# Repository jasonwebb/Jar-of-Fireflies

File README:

# Jar of Fireflies

Reinvention of the classic "Jar of fireflies" project using the Arduino framework and the ATTiny85 microcontroller. Includes six charlieplexed LEDs, a piezo sensor and a variety of powering options.

Mason jars outfitted with LEDs and a small microcontroller programmed to mimic the behavior of fireflies caught on a warm summer night. The addition of a piezo sensor enables a degree of interactivity that everyone wished their jars did as kids; tap the jar, and the lights react! Based on an old project found on Instructables, this project includes a number of great updates, including Arduino compatibility, interactivity and easier-to-use parts! Plus, the entire project embraces the principles of Open Source Hardware (OSHW), which means you can learn from and modify all of the code, design files, schematics and more for free!

## Board features
* ATTiny85 microcontroller mounted with a DIP IC socket, so it can be easily removed and reprogrammed externally using HLT's Arduino bootloader (see http://hlt.media.mit.edu/?p=1695).
* Six charlieplexed LEDs (with the option to use SMD LEDs with fancy soldering).
* Piezo sensor to detect tapping for interaction.
* 2-pin header for power, so external breakout boards for various power options can be added (DC barrel jack, USB mini-B, 2xAA batteries and solar cell).
* Contacts for alligator clips so multiple jars can be daisychained to a single power source.

## More information
* Author website: http://jason-webb.info
* Wiki: http://jason-webb.info/wiki/index.php?title=Jar_of_Fireflies

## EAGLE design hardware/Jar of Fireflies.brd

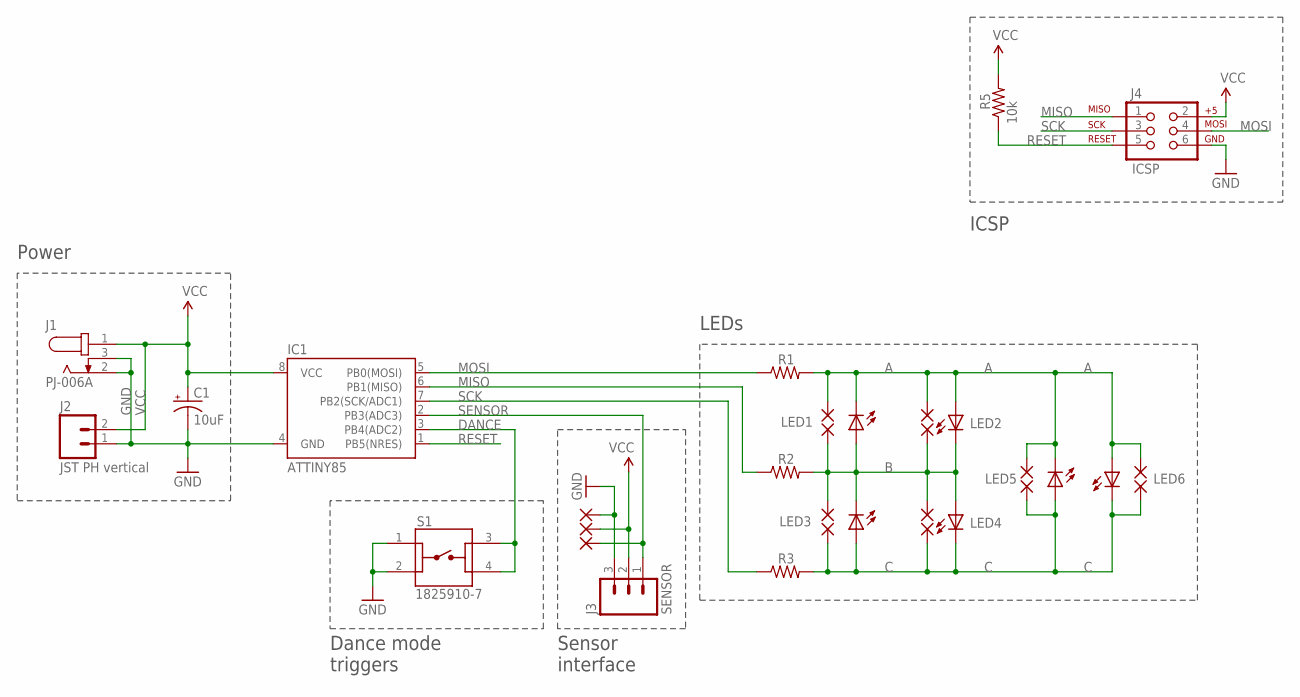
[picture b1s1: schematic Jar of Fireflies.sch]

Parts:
C1: 10uF; CPOL-RADIAL-10UF-25V
IC1: ATTINY85; DIP08
J1: PJ-006A; CUI_PJ-006A
J2: JST PH vertical; JST-2-PTH-VERT
J3: SENSOR; 1X03
J4: ICSP; 2X3_LOCK
LED1, LED2, LED3, LED4, LED5, LED6: Amber; LED5MM
PAD1, PAD2, PAD3, PAD4, PAD5, PAD6, PAD7, PAD8, PAD9, PAD10, PAD11, PAD12: SMD2; SMD1,27-2,54
PAD13, PAD14, PAD15: WIREPADSMD1,27-254; SMD1,27-2,54
R1, R2, R3: 150; 0207/2V
R5: 10k; 0207/2V
S1: 1825910-7; SW_1825910-7

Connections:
A: LED1.K (C), LED2.A, LED5.K (C), LED6.A, PAD1.1, PAD5.1, PAD9.1, PAD11.1, R1.2
B: LED1.A, LED2.K (C), LED3.K (C), LED4.A, PAD2.1, PAD3.1, PAD6.1, PAD7.1, R2.2
C: LED3.A, LED4.K (C), LED5.A, LED6.K (C), PAD4.1, PAD8.1, PAD10.1, PAD12.1, R3.2
DANCE: IC1.3 (PB4(ADC2)), S1.3, S1.4
GND: C1.2 (-), IC1.4 (GND), J1.2, J1.3, J2.1, J3.3, J4.6, PAD13.1, S1.1, S1.2
MISO: IC1.6 (PB1(MISO)), J4.1, R2.1
MOSI: IC1.5 (PB0(MOSI)), J4.4, R1.1
RESET: IC1.1 (PB5(NRES)), J4.5, R5.1
SCK: IC1.7 (PB2(SCK/ADC1)), J4.3, R3.1
SENSOR: IC1.2 (PB3(ADC3)), J3.1, PAD15.1
VCC: C1.1 (+), IC1.8 (VCC), J1.1, J2.2, J3.2, J4.2, PAD14.1, R5.2

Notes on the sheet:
ICSP
Power
Dance mode triggers
Sensor interface
LEDs

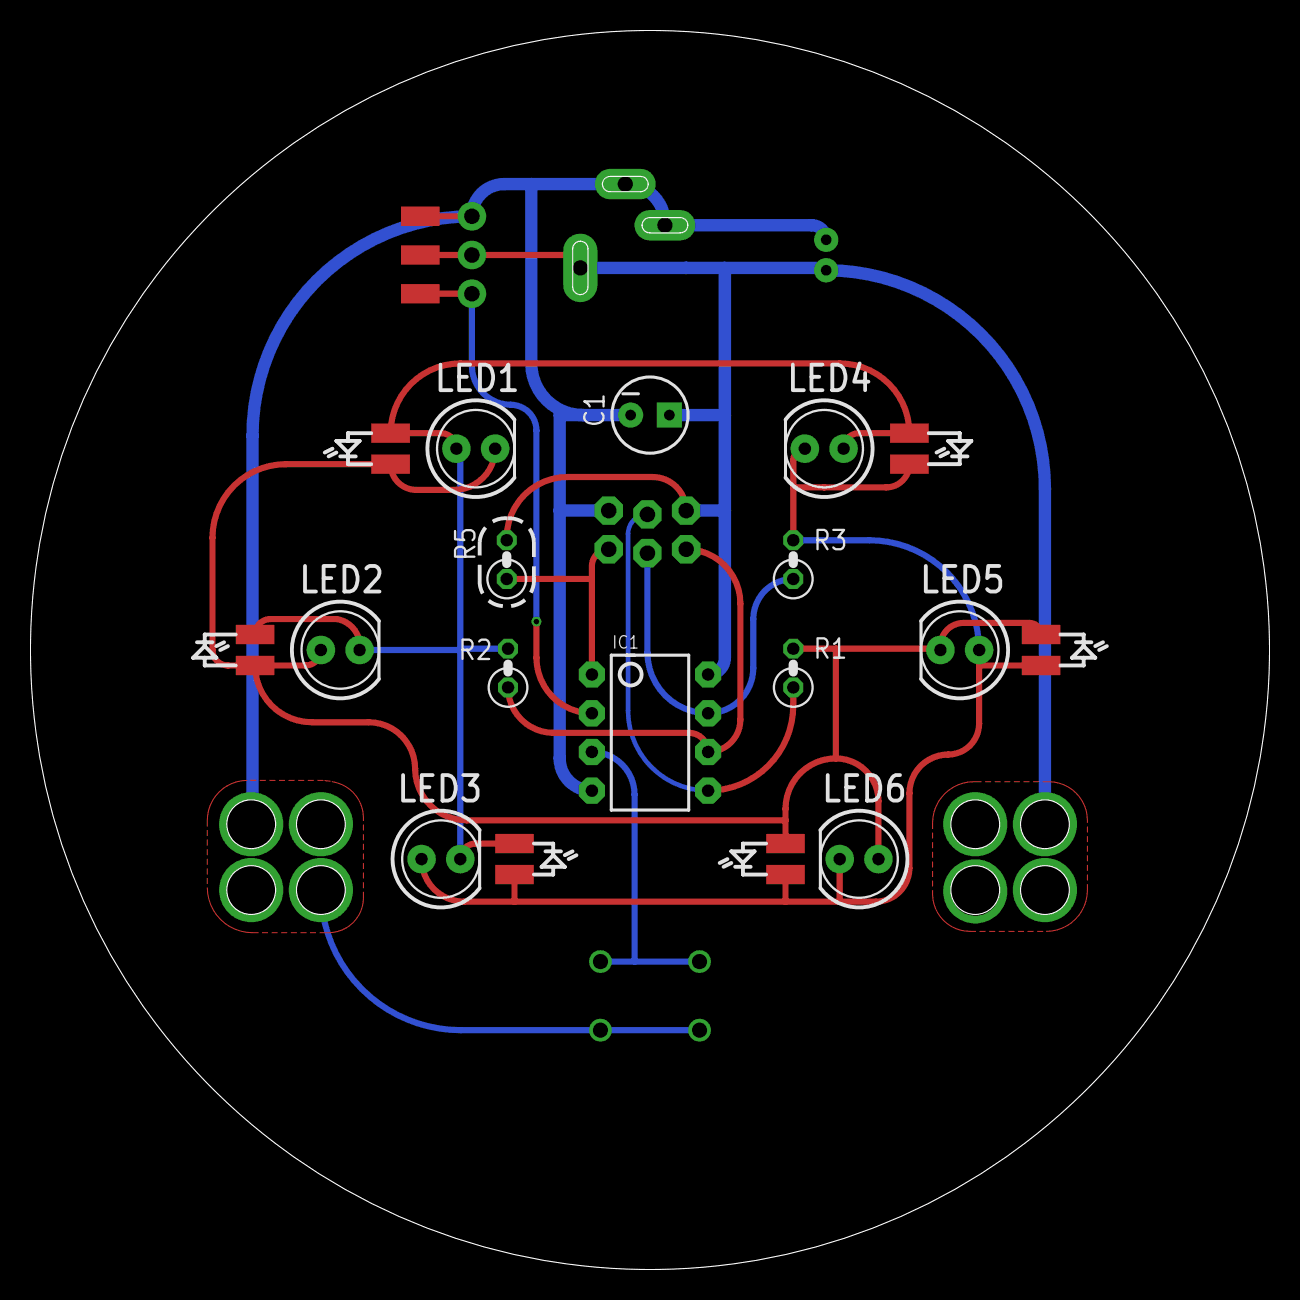
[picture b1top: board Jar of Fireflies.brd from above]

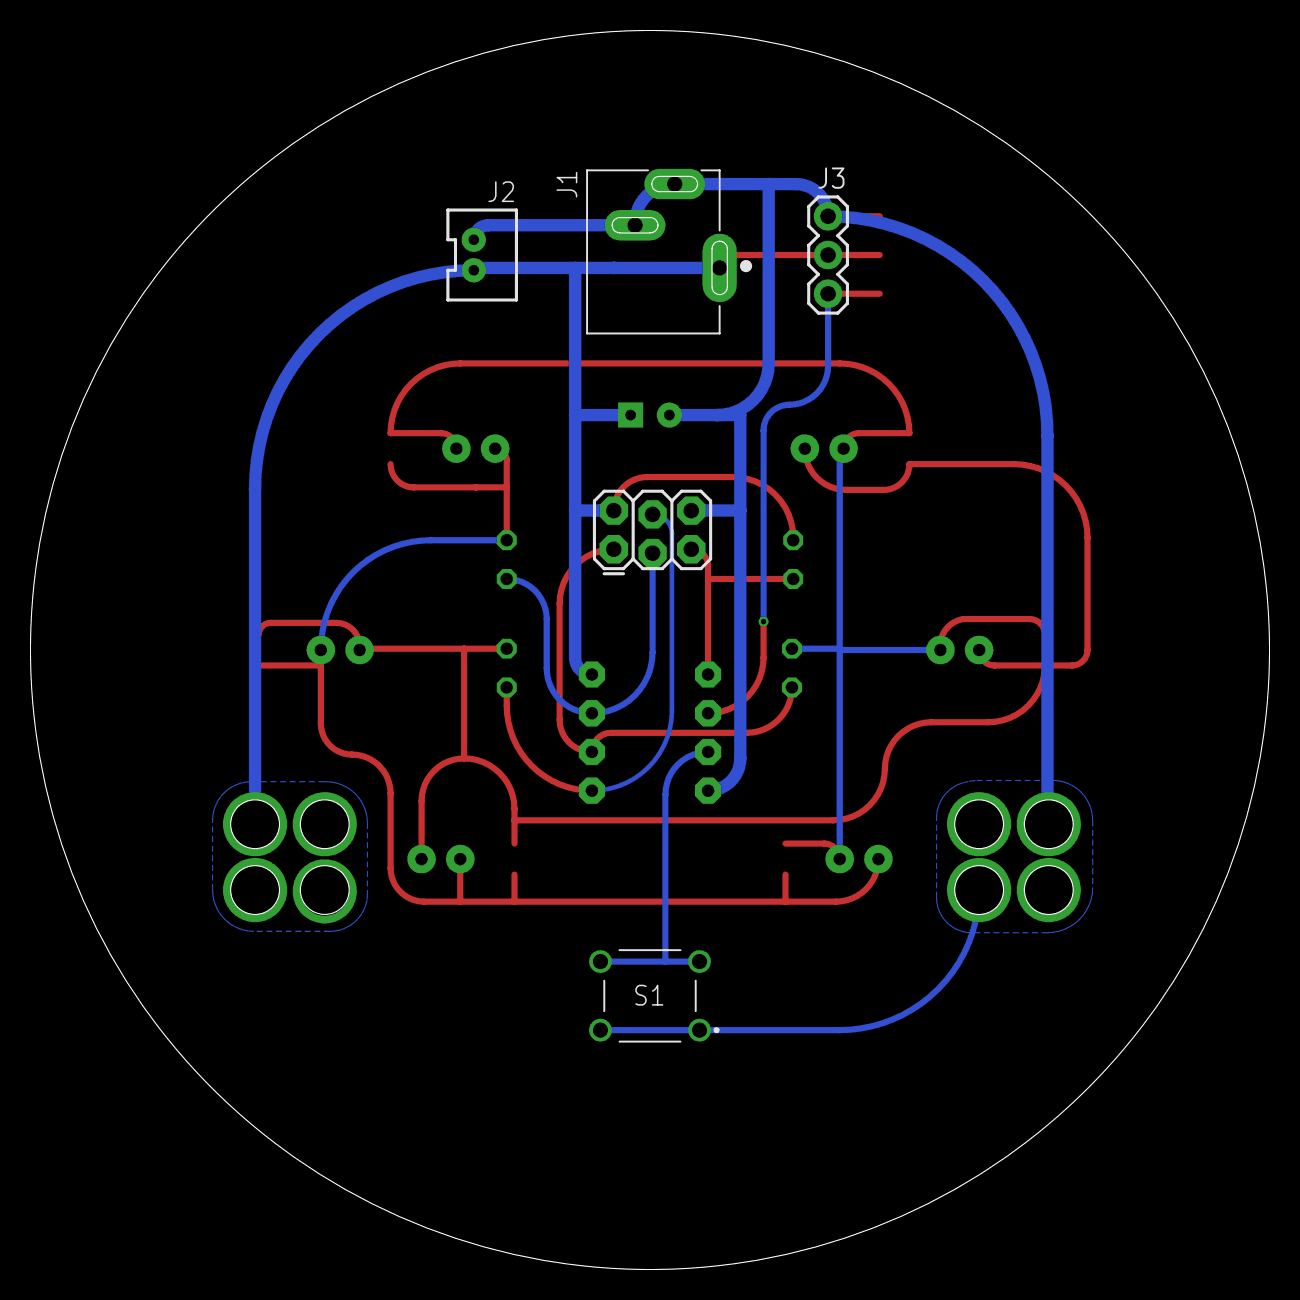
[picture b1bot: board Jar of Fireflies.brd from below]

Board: 2 copper layers, 81.3 x 81.3 mm, 32 parts (5 on the bottom side), 11 nets.

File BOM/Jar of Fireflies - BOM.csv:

ID,Name,Purpose,Qty,Cost @ 1,Cost @ 25,Cost @ 50,Cost @ 100,Total @ 1,Total @ 25,Total @ 50,Total @ 100,Part number,URL
IC1,ATTINY85-20PU-ND,Microcontroller,1,$1.24,$1.33,$1.33,$1.03,$1.24,$1.33,$1.33,$1.03,ATTINY85-20PU-ND,https://www.digikey.com/product-detail/en/microchip-technolo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
,8-pin DIP IC socket,Holds ATTiny85,1,$0.18,$0.15,$0.15,$0.13,$0.18,$0.15,$0.15,$0.13,AE9986-ND,https://www.digikey.com/product-detail/en/assmann-wsw-compon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
C1,10uF 50V aluminum capacitor,Power smoothing,1,$0.23,$0.15,$0.15,$0.08,$0.23,$0.15,$0.15,$0.08,P10425CT-ND,https://www.digikey.com/product-detail/en/panasonic-electron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
R1-R3,"150ohm, 1/4W resistor",Current limits for LEDs,3,$0.10,$0.03,$0.02,$0.02,$0.30,$0.09,$0.07,$0.05,CF14JT150RCT-ND,https://www.digikey.com/product-detail/en/stackpole-electron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
R4,"1M, 1/4W resistor",Piezo drain,1,$0.10,$0.03,$0.02,$0.02,$0.10,$0.03,$0.02,$0.02,CF14JT1M00CT-ND,https://www.digikey.com/product-detail/en/stackpole-electron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
R5,"10k, 1/4W resistor",Pull-up for ICSP RESET pin,1,$0.10,$0.03,$0.02,$0.02,$0.10,$0.03,$0.02,$0.02,CF14JT10K0CT-ND,https://www.digikey.com/product-detail/en/stackpole-electron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
LED1-6,"Amber LED, 2.1V @ 20mA, 5mm",Fireflies,6,$0.28,$0.28,$0.28,$0.25,$1.68,$1.68,$1.68,$1.49,C566C-AFF-CU0W0252CT-ND,https://www.digikey.com/product-detail/en/cree-inc/C566C-AFF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
J1,3.5mm DC power jack,Wall and solar power,1,$0.78,$0.65,$0.62,$0.59,$0.78,$0.65,$0.62,$0.59,CP-006A-ND,https://www.digikey.com/product-detail/en/cui-inc/PJ-006A/CP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
J2,2-pin JST PH vertical jack,Battery pack input,1,$0.17,$0.16,$0.16,$0.10,$0.17,$0.16,$0.16,$0.10,455-1704-ND,https://www.digikey.com/products/en?mpart=B2B-PH-K-S%28LF%29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
J3,"3-pin 0.1"" male header",Sensor interface,1,$0.13,$0.09,$0.07,$0.07,$0.13,$0.09,$0.07,$0.07,732-5316-ND,https://www.digikey.com/product-detail/en/wurth-electronics-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
J4,"2x3-pin 0.1"" male header",ICSP interface,1,,,,,$0.00,$0.00,$0.00,$0.00,Not to be permanently soldered to board - just press-fit into ICSP plug,
PIEZO,Piezo element,Trigger for 'dance' mode,1,$0.98,$0.71,$0.67,$0.62,$0.98,$0.71,$0.67,$0.62,445-172991-ND,https://www.digikey.com/product-detail/en/tdk-corporation/PS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
S1,Momentary switch,Manual trigger for 'dance' mode,1,$0.01,$0.10,$0.10,$0.09,$0.01,$0.10,$0.10,$0.09,450-1804-ND,https://www.digikey.com/product-detail/en/te-connectivity-al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
,,,,,,,,,,,,,
,,,,,,,Total,$5.90,$5.17,$5.04,$4.28,,

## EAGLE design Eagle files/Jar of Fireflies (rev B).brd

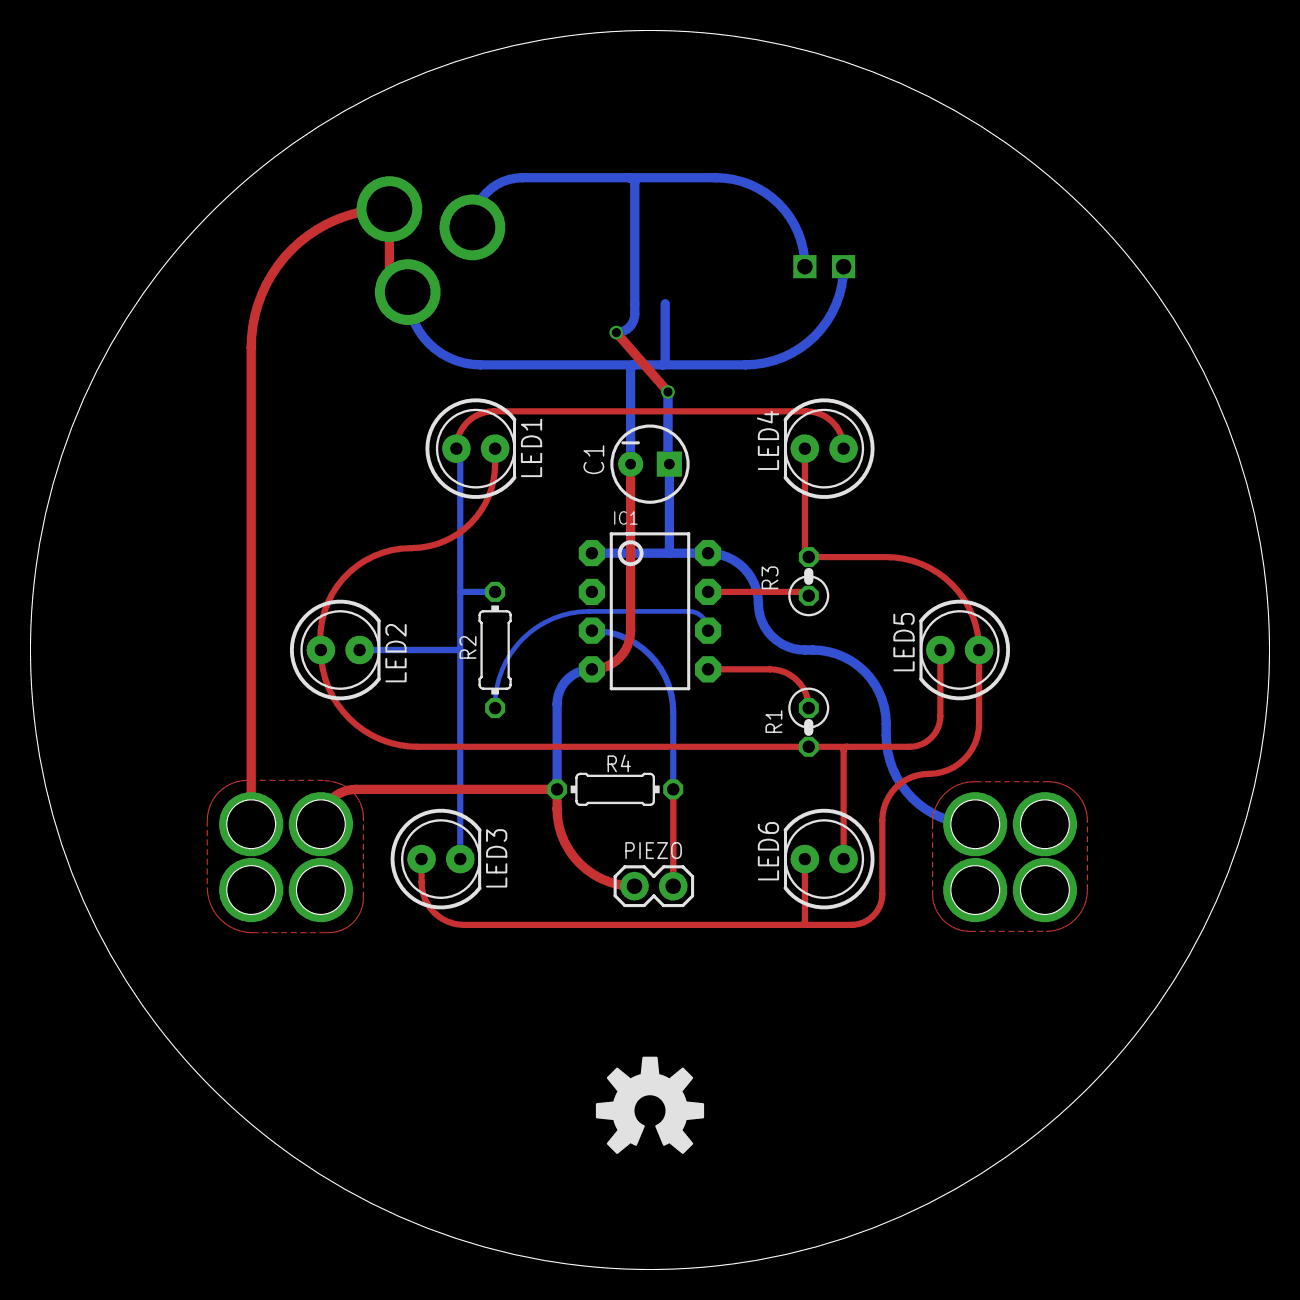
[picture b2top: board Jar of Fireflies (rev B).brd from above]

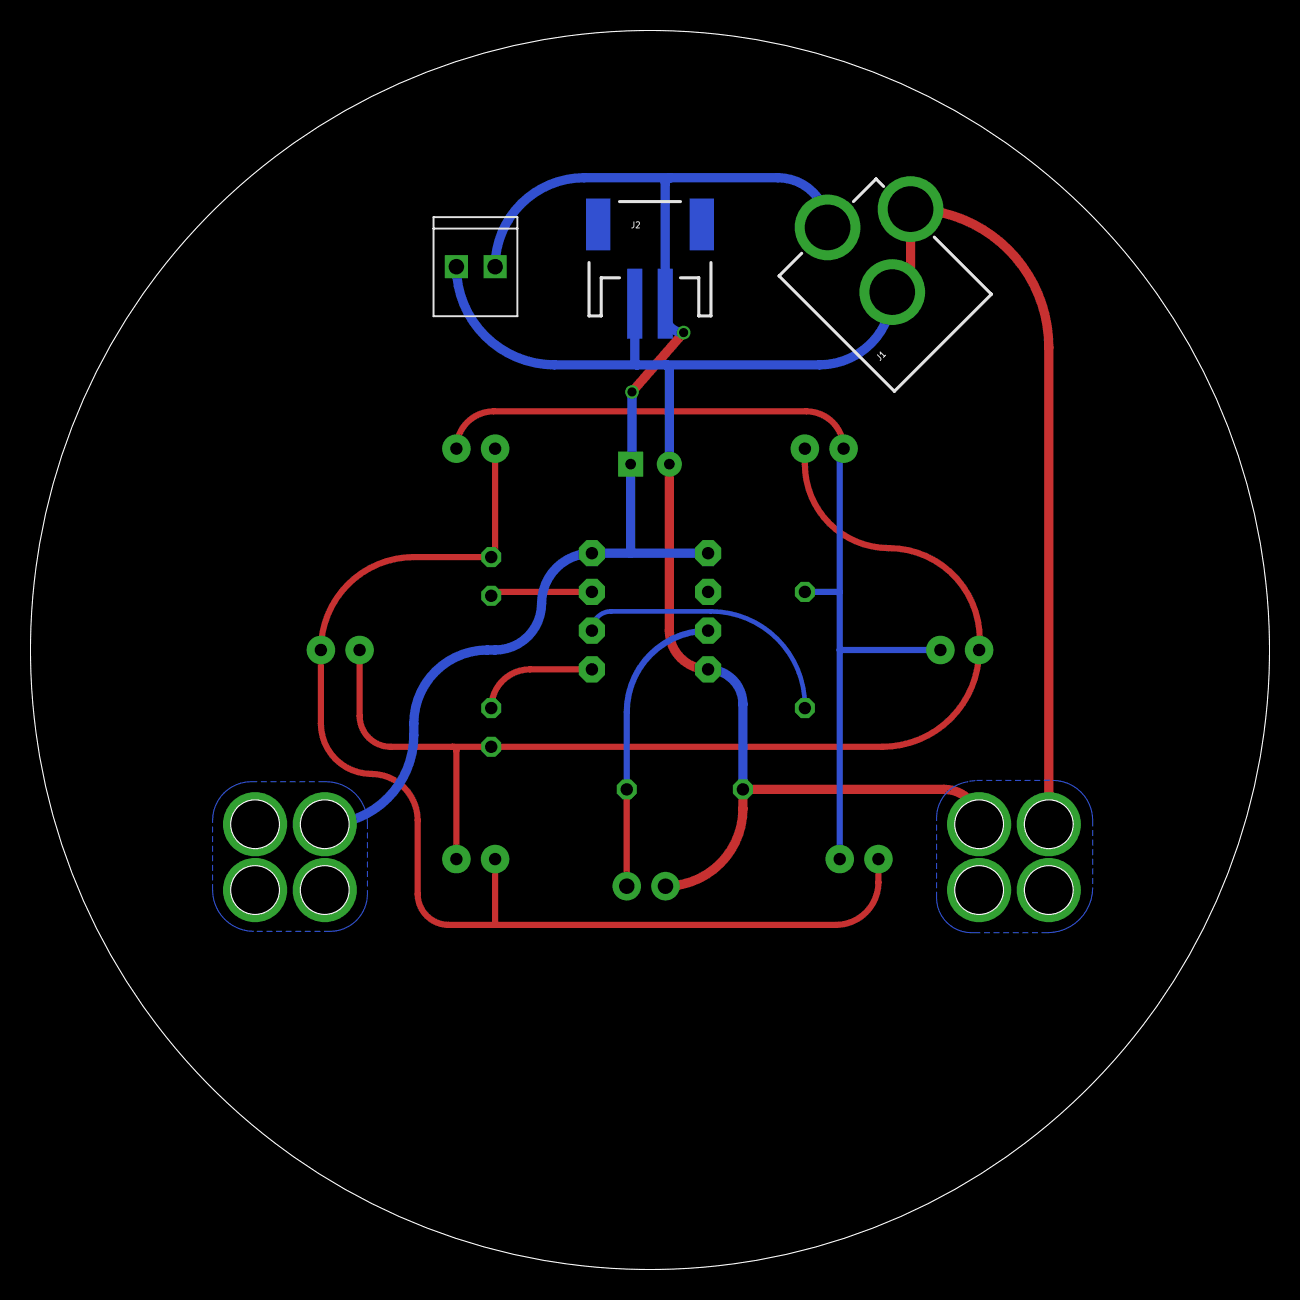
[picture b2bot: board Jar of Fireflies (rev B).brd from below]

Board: 2 copper layers, 81.3 x 81.3 mm, 17 parts (3 on the bottom side), 9 nets.

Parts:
C1: 10uF; CPOL-RADIAL-10UF-25V
IC1: ATTINY85; DIP08
J1: POWER_JACKPTH; POWER_JACK_PTH
J2: JST-2-SMD
J3: M022.54MM_SCREWTERM; 1X02_2.54_SCREWTERM
LED1, LED2, LED3, LED4, LED5, LED6: LED5MM
LOGO1: OSHW-LOGOL; OSHW-LOGO-L
PIEZO: 1X02
R1, R3: 150; 0207/2V
R2: 150; 0204/7
R4: 1M; 0204/7

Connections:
GND: C1.2, IC1.4, J1.GND, J1.GNDBREAK, J2.1, J3.P2, PIEZO.1, R4.1
unnamed: LED1.A, LED2.K, LED3.K, LED4.A, R2.2
unnamed: LED1.K, LED2.A, LED5.K, LED6.A, R1.2
unnamed: LED3.A, LED4.K, LED5.A, LED6.K, R3.2
PIEZO: IC1.3, PIEZO.2, R4.2
PORTA: IC1.5, R1.1
PORTB: IC1.6, R2.1
PORTC: IC1.7, R3.1
VCC: C1.1, IC1.1, IC1.8, J1.PWR, J2.2, J3.P1

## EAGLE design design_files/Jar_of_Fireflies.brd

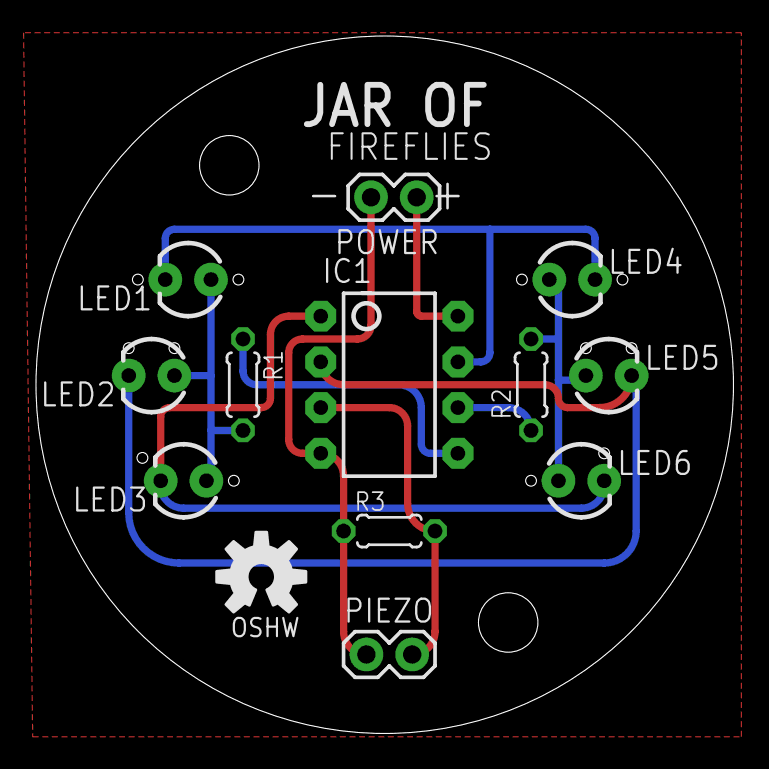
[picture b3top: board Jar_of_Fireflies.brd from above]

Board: 2 copper layers, 38.7 x 38.7 mm, 15 parts (0 on the bottom side), 10 nets.

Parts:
IC1: ATTINY85; DIP08
JP1, JP2: STAND-OFF
LED1, LED2, LED3, LED4, LED5, LED6: LED3MM
PIEZO: 1X02
POWER: 1X02
R1, R2, R3: 0204/5
U$3: OSHW-LOGO-M

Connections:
1+: IC1.5, R1.1
1-: IC1.7, LED1.K, LED4.K
2+: IC1.6, R2.1
2-: IC1.2, LED2.K, LED5.K
3-: IC1.1, LED3.K, LED6.K
GND: IC1.4, PIEZO.1, POWER.2, R3.1
unnamed: LED1.A, LED2.A, LED3.A, R1.2
unnamed: LED4.A, LED5.A, LED6.A, R2.2
PIEZO: IC1.3, PIEZO.2, R3.2
VCC: IC1.8, POWER.1

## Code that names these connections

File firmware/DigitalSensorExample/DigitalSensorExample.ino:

/*
  Jar of Fireflies with external sensor

  DESCRIPTION:
    All the same features as the base "Jar of Fireflies" 
    firmware, but with the addition of support for a
    simple external digital sensor. See README.md for notes.
*/

// Pin assignments
const byte pinA = 0;        // Physical pin 5 (PB0, MOSI, PWM)
const byte pinB = 1;        // Physical pin 6 (PB1, MISO, PWM)
const byte pinC = 2;        // Physical pin 7 (PB2, SCK, ADC1)
const byte triggerPin = 4;  // Physical pin 3 (ADC2)
const byte sensorPin = 3;   // Physical pin 2 (PB3, ADC3)

// LED variables
byte currentLED;        // Number of currently active LED (1-6)
byte previousLED = -1;  // Last LED flashed so we can avoid flashing it twice in a row
byte rampUpSpeed;       // Randomly generated value for fading in LEDs
byte rampDownSpeed;     // Randomly generated value for fading out LEDs
byte numBlinks;         // Randomly generated value for number of times to flash LED whe fully faded in
int brightness;         // Current brightness (0-255) of currently active LED

// "Dance mode" trigger variables
const int triggerBufferSize = 10;      // Number of readings to store
int triggerValues[triggerBufferSize];  // Last n values of triggers
int triggerThreshold = 1;              // Minimum average value to trigger "dance mode"
int triggerCounter = 0;                // Current index in buffer array, used when filling it with readings

// Sensor variables
int sensorState = LOW;          // Current state of external sensor
int previousSensorState = LOW;  // Previous sensor state, used to track changes in state

// Program states
const byte BEGIN = 0;         // Sets up program for a new cycle
const byte RAMP_UP = 1;       // Fades in current LED
const byte BLINKING = 2;      // Blinks the current LED when at full brightness
const byte RAMP_DOWN = 3;     // Fades out the current LED
const byte DANCE = 4;         // Flashes LEDs in fun pattern
byte CURRENT_ACTION = BEGIN;  // Start program off in BEGIN mode

void setup() {
  turnOffAll();  // Flush any stray current from the ports

  // Set up the external sensor pin as input
  pinMode(sensorPin, INPUT);
}

void loop() {
  switch (CURRENT_ACTION) {

    // BEGIN ===========================================
    // Set up all the variables to flash a new LED
    case BEGIN:
      // Choose a new LED
      previousLED = currentLED;

      // Make sure it's different than the last one
      do {
        currentLED = (int) random(1, 6);
      } while (currentLED == previousLED);

      // Randomize the number of times to blink
      numBlinks = (int) random(1, 6);

      // Randomize the fade in and fade out speeds
      rampUpSpeed = random(6);
      rampDownSpeed = rampUpSpeed * 2;

      brightness = 0;
      CURRENT_ACTION = RAMP_UP;
      break;

    // RAMP UP ========================================
    // Fade in the LED
    case RAMP_UP:
      analogOn(currentLED, brightness);
      delay(rampUpSpeed);

      if (brightness >= 255) {
        CURRENT_ACTION = BLINKING;
        brightness = 0;
      } else {
        brightness++;
      }

      break;

    // BLINKING ====================================
    // Blink the LED a certain number of times
    case BLINKING:
      analogOn(currentLED, 0);
      delay(random(10, 50));
      analogOn(currentLED, 255);
      delay(random(30, 100));

      if (numBlinks > 0) {
        numBlinks--;
      } else {
        CURRENT_ACTION = RAMP_DOWN;
        brightness = 255;
      }

      break;

    // RAMP DOWN ===========================================
    // Fade out the LED
    case RAMP_DOWN:
      analogOn(currentLED, brightness);
      delay(rampDownSpeed);

      if (brightness == 0) {
        CURRENT_ACTION = BEGIN;
      } else {
        brightness--;
      }

      break;

    // DANCE ==============================================
    // Flash each LED, one at a time, six times in a row
    case DANCE:
      for (int j = 0; j < 6; j++) {
        for (int i = 1; i <= 6; i++) {
          turnOn(i);
          delay(50);
          turnOff(i);
          delay(50);
        }
      }

      // Clear the trigger value buffer so dance mode isn't immediately retriggered
      for(int i = 0; i < triggerBufferSize; i++) {
        triggerValues[i] = 0;
      }

      CURRENT_ACTION = BEGIN;

      break;
  }

  // Poll the "dance mode" triggers
  checkDanceTriggers();

  // Poll the sensor
  checkSensor();
}

// Turn on a single LED to full brightness
void turnOn(byte led) {
  analogOn(led, 255);
}

// Turn off an LED completely
void turnOff(byte led) {
  analogOn(led, 0);
}

// Turn off all LEDs and drain any remaining current
void turnOffAll() {
  for (int i = 0; i <= 2; i++) {
    pinMode(i, OUTPUT);
    digitalWrite(i, LOW);
  }
}

// Write an analog value to an LED
void analogOn(byte led, byte value) {
  switch (led) {
    case 1:
      pinMode(pinA, OUTPUT);
      pinMode(pinB, OUTPUT);
      pinMode(pinC, INPUT);

      digitalWrite(pinA, LOW);
      analogWrite(pinB, value);
      break;
    case 2:
      pinMode(pinA, OUTPUT);
      pinMode(pinB, OUTPUT);
      pinMode(pinC, INPUT);

      digitalWrite(pinB, LOW);
      analogWrite(pinA, value);
      break;
    case 3:
      pinMode(pinA, INPUT);
      pinMode(pinB, OUTPUT);
      pinMode(pinC, OUTPUT);

      digitalWrite(pinC, HIGH);
      analogWrite(pinB, 255 - value);
      break;
    case 4:
      pinMode(pinA, INPUT);
      pinMode(pinB, OUTPUT);
      pinMode(pinC, OUTPUT);

      digitalWrite(pinC, LOW);
      analogWrite(pinB, value);
      break;
    case 5:
      pinMode(pinA, OUTPUT);
      pinMode(pinB, INPUT);
      pinMode(pinC, OUTPUT);

      digitalWrite(pinC, HIGH);
      analogWrite(pinA, 255 - value);
      break;
    case 6:
      pinMode(pinA, OUTPUT);
      pinMode(pinB, INPUT);
      pinMode(pinC, OUTPUT);

      digitalWrite(pinC, LOW);
      analogWrite(pinA, value);
      break;
  }
}

// Poll the "dance mode" triggers to find out if program state needs to change
void checkDanceTriggers() {
  // Fill up the buffer with readings
  if (triggerCounter < triggerBufferSize) {
    int val = analogRead(triggerPin);
    triggerValues[triggerCounter] = val;
    triggerCounter++;
    return;
  }

  // Once the buffer is full, find the average
  int avg = 0;

  for (int i = 0; i < triggerBufferSize; i++)
    avg += triggerValues[i];

  avg = avg / triggerBufferSize;

  // If the average is above the threshold, initiate "dance mode" state
  if (avg >= triggerThreshold) {
    CURRENT_ACTION = DANCE;
  }

  // Reset counter
  triggerCounter = 0;
}

// Read the external sensor pin to find out if a trigger event has happened
void checkSensor() {
  previousSensorState = sensorState;
  sensorState = digitalRead(sensorPin);

  // Sensor state has changed from LOW to HIGH, so it's time to dance!
  if(sensorState == HIGH && previousSensorState != sensorState) {
    CURRENT_ACTION = DANCE;
  }
}

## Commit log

2012-02-25 First commit of Eagle files
2012-02-27 Updated folder name
2012-02-27 Removing old Eagle folder
2012-12-19 Overdue updates
2012-12-19 Removing old README
2012-12-19 Test
2012-12-19 Adding README
2012-12-19 Goddamn README
2013-01-01 Added BOMs
2014-02-08 Added Arduino sketch
2014-03-01 Updated BOM and Eagle files for rev B
2014-03-01 Added images of schematic + PCB design
2015-06-26 Updated Eagle files
    Better silkscreen, more power options.
2017-01-15 Updated folder and file names
2017-01-18 Added README to hardware/
2017-01-20 README update
2018-08-24 Updating PCB design with ICSP, SMD pads for LEDs, sensor interface, and different power options
2018-08-24 Updating references to PCB renders
2018-08-25 Changing image URLs to absolute so they display
2018-08-25 Adding WIP warning to main README
2018-08-28 Switching to vertical JST jack
2018-08-31 Updating custom libraries, adding new tactile pushbutton
2018-08-31 Replacing pushbutton with sourced one
2018-08-31 Updating BOM with components for newest design
2018-09-04 Flipping bitmap silkscreen
2018-09-08 Adding .gitignore
2018-09-08 Updating license notes, features, and description
2018-09-08 Abstracting piezo trigger to account for tactile button, improing comments
2018-09-14 Adding sketch example for simple external digital sensors.
2018-09-14 Tweaking comment in firmware
2018-09-14 Adding generic example of external analog sensor
2018-09-18 Adding missing part (R5) to BOM
2018-11-27 Refactoring dance mode away from piezo to use button only
2018-11-27 Removing piezo from PCB, making button switch to GND, adding solder pads to sensor interface
2018-11-27 Documenting dance button setup code
2018-11-27 Adding circuit renders to main README
2019-02-20 Removing references to built-in piezo sensor that is now removed

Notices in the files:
parts and their libraries:
SparkFun-Connectors: Licensing: CC v3.0 Share-Alike You are welcome to use this library for commercial purposes.
SparkFun-Aesthetics: Licensing: Creative Commons ShareAlike 4.0 International - https://creativecommons.org/licenses/by-sa/4.0
